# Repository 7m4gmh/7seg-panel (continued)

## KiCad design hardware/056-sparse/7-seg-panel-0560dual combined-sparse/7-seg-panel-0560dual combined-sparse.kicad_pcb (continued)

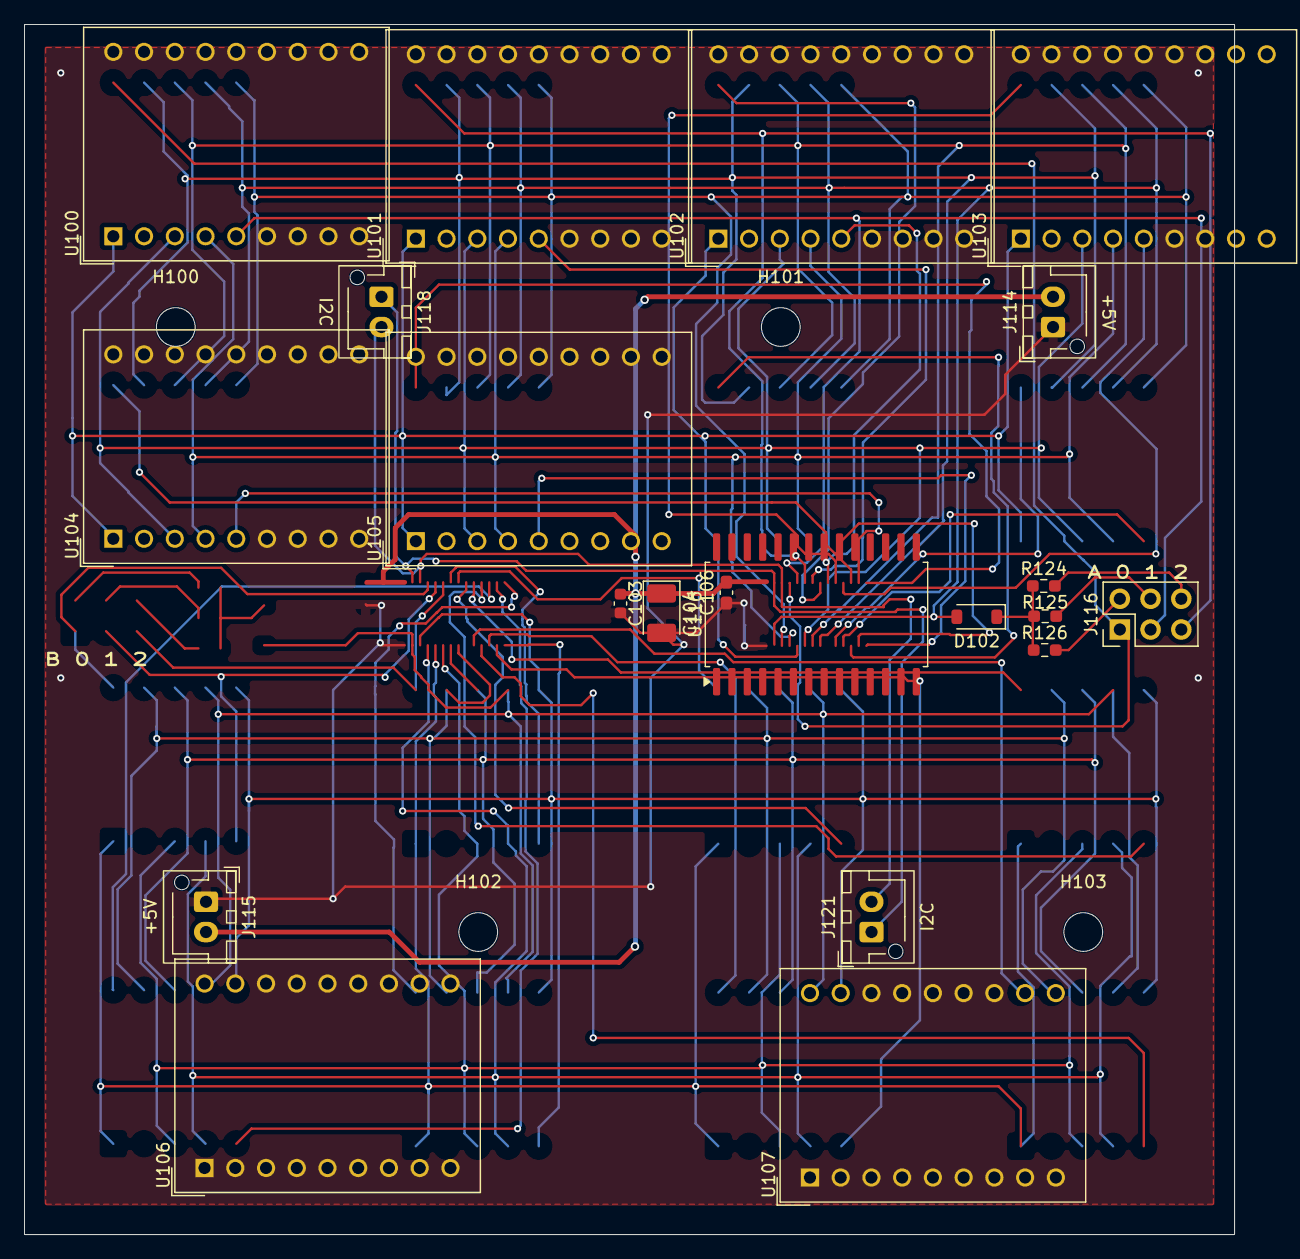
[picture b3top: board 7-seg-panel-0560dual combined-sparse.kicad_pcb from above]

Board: 2 copper layers, 100.0 x 100.0 mm, 25 parts (0 on the bottom side), 31 nets.

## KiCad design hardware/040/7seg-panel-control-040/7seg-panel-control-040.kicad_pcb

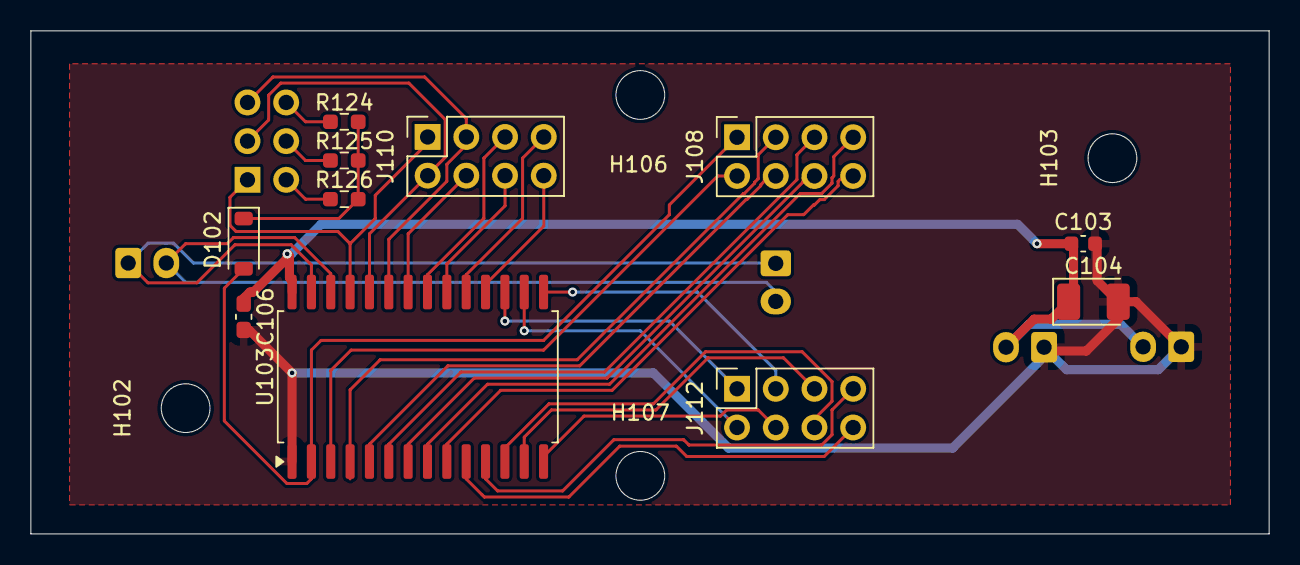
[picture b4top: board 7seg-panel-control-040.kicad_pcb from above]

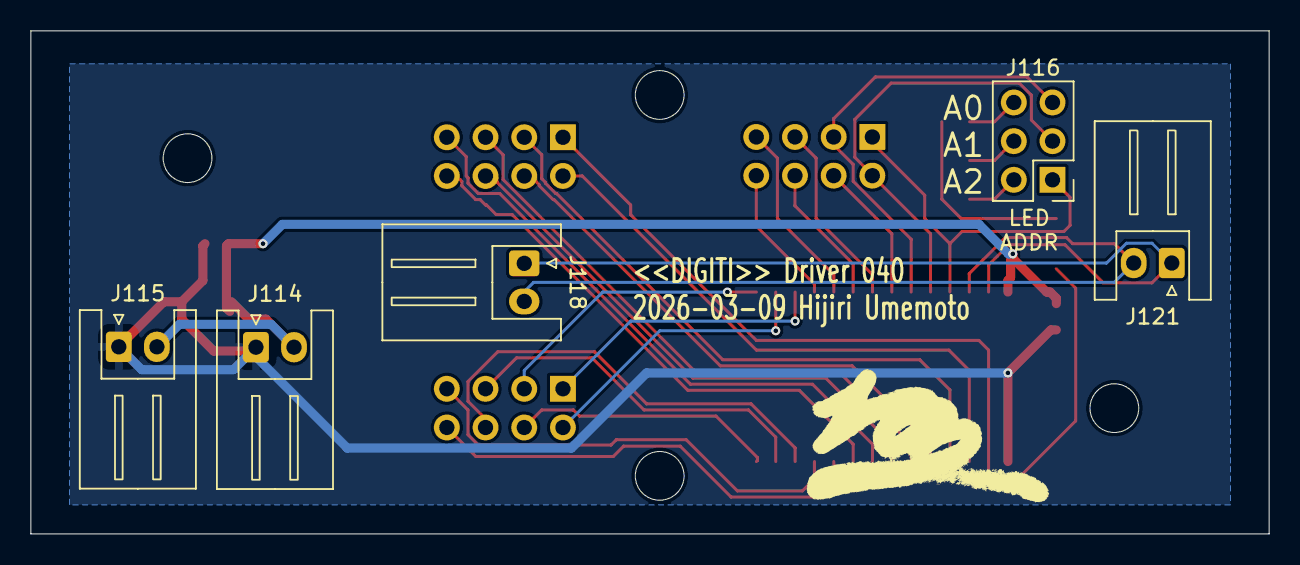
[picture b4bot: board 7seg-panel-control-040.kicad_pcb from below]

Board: 2 copper layers, 81.3 x 33.0 mm, 20 parts (5 on the bottom side), 32 nets.

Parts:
C103: 22uF; C_0603_1608Metric
C104: 22uF; CP_EIA-3528-21_Kemet-B_HandSolder
C106: 0.1uF; C_0603_1608Metric_Pad1.08x0.95mm_HandSolder
D102: 1N4148W; D_SOD-123
H102, H103, H106, H107: MountingHole; MountingHole_3.2mm_M3
J108, J110, J112: Conn_02x04_Odd_Even; PinSocket_2x04_P2.54mm_Vertical
J114, J115: +5V; JST_XH_S2B-XH-A_1x02_P2.50mm_Horizontal
J116: Conn_02x03_Odd_Even; PinHeader_2x03_P2.54mm_Vertical
J118, J121: I2C; JST_XH_S2B-XH-A_1x02_P2.50mm_Horizontal
R124, R125, R126: 39kR; R_0603_1608Metric_Pad0.98x0.95mm_HandSolder
U103: HT16K33-28-SOPA; SOP-28_8.4x18.16mm_P1.27mm

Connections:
COM0: D102.2 (A), J108.1, U103.2 (COM0/AD)
COM1: J108.2, U103.3 (COM1/KS0)
COM2: J108.3, U103.4 (COM2/KS1)
COM3: J108.4, U103.5 (COM3/KS2)
COM4: J108.5, U103.6 (COM4)
COM5: J108.6, U103.7 (COM5)
COM6: J108.7, U103.8 (COM6)
COM7: J108.8, U103.9 (COM7)
GND: C103.2, C104.2, C106.2, J114.1, J115.1, U103.1 (VSS)
unnamed: D102.1 (K), R124.1, R125.1, R126.1
unnamed: J116.2, R126.2
unnamed: J116.4, R125.2
unnamed: J116.6, R124.2
ROW0: J110.1, J116.1, U103.25 (ROW0/A2)
ROW1: J110.2, J116.3, U103.24 (ROW1/A1)
ROW2: J110.3, J116.5, U103.23 (ROW2/A0)
ROW3: J110.4, U103.22 (ROW3/K1)
ROW4: J110.5, U103.21 (ROW4/K2)
ROW5: J110.6, U103.20 (ROW5/K3)
ROW6: J110.7, U103.19 (ROW6/K4)
ROW7: J110.8, U103.18 (ROW7/K5)
ROW8: J112.1, U103.17 (ROW8/K6)
ROW9: J112.2, U103.16 (ROW9/K7)
ROW10: J112.3, U103.15 (ROW10/K8)
ROW11: J112.4, U103.14 (ROW11/K9)
ROW12: J112.5, U103.13 (ROW12/K10)
ROW13: J112.6, U103.12 (ROW13/K12)
ROW14: J112.7, U103.11 (ROW14/K12)
ROW15: J112.8, U103.10 (ROW15/K13/INT)
SCL: J118.2, J121.2, U103.26 (SCL)
SDA: J118.1, J121.1, U103.27 (SDA)
VDD: C103.1, C104.1, C106.1, J114.2, J115.2, U103.28 (VDD)

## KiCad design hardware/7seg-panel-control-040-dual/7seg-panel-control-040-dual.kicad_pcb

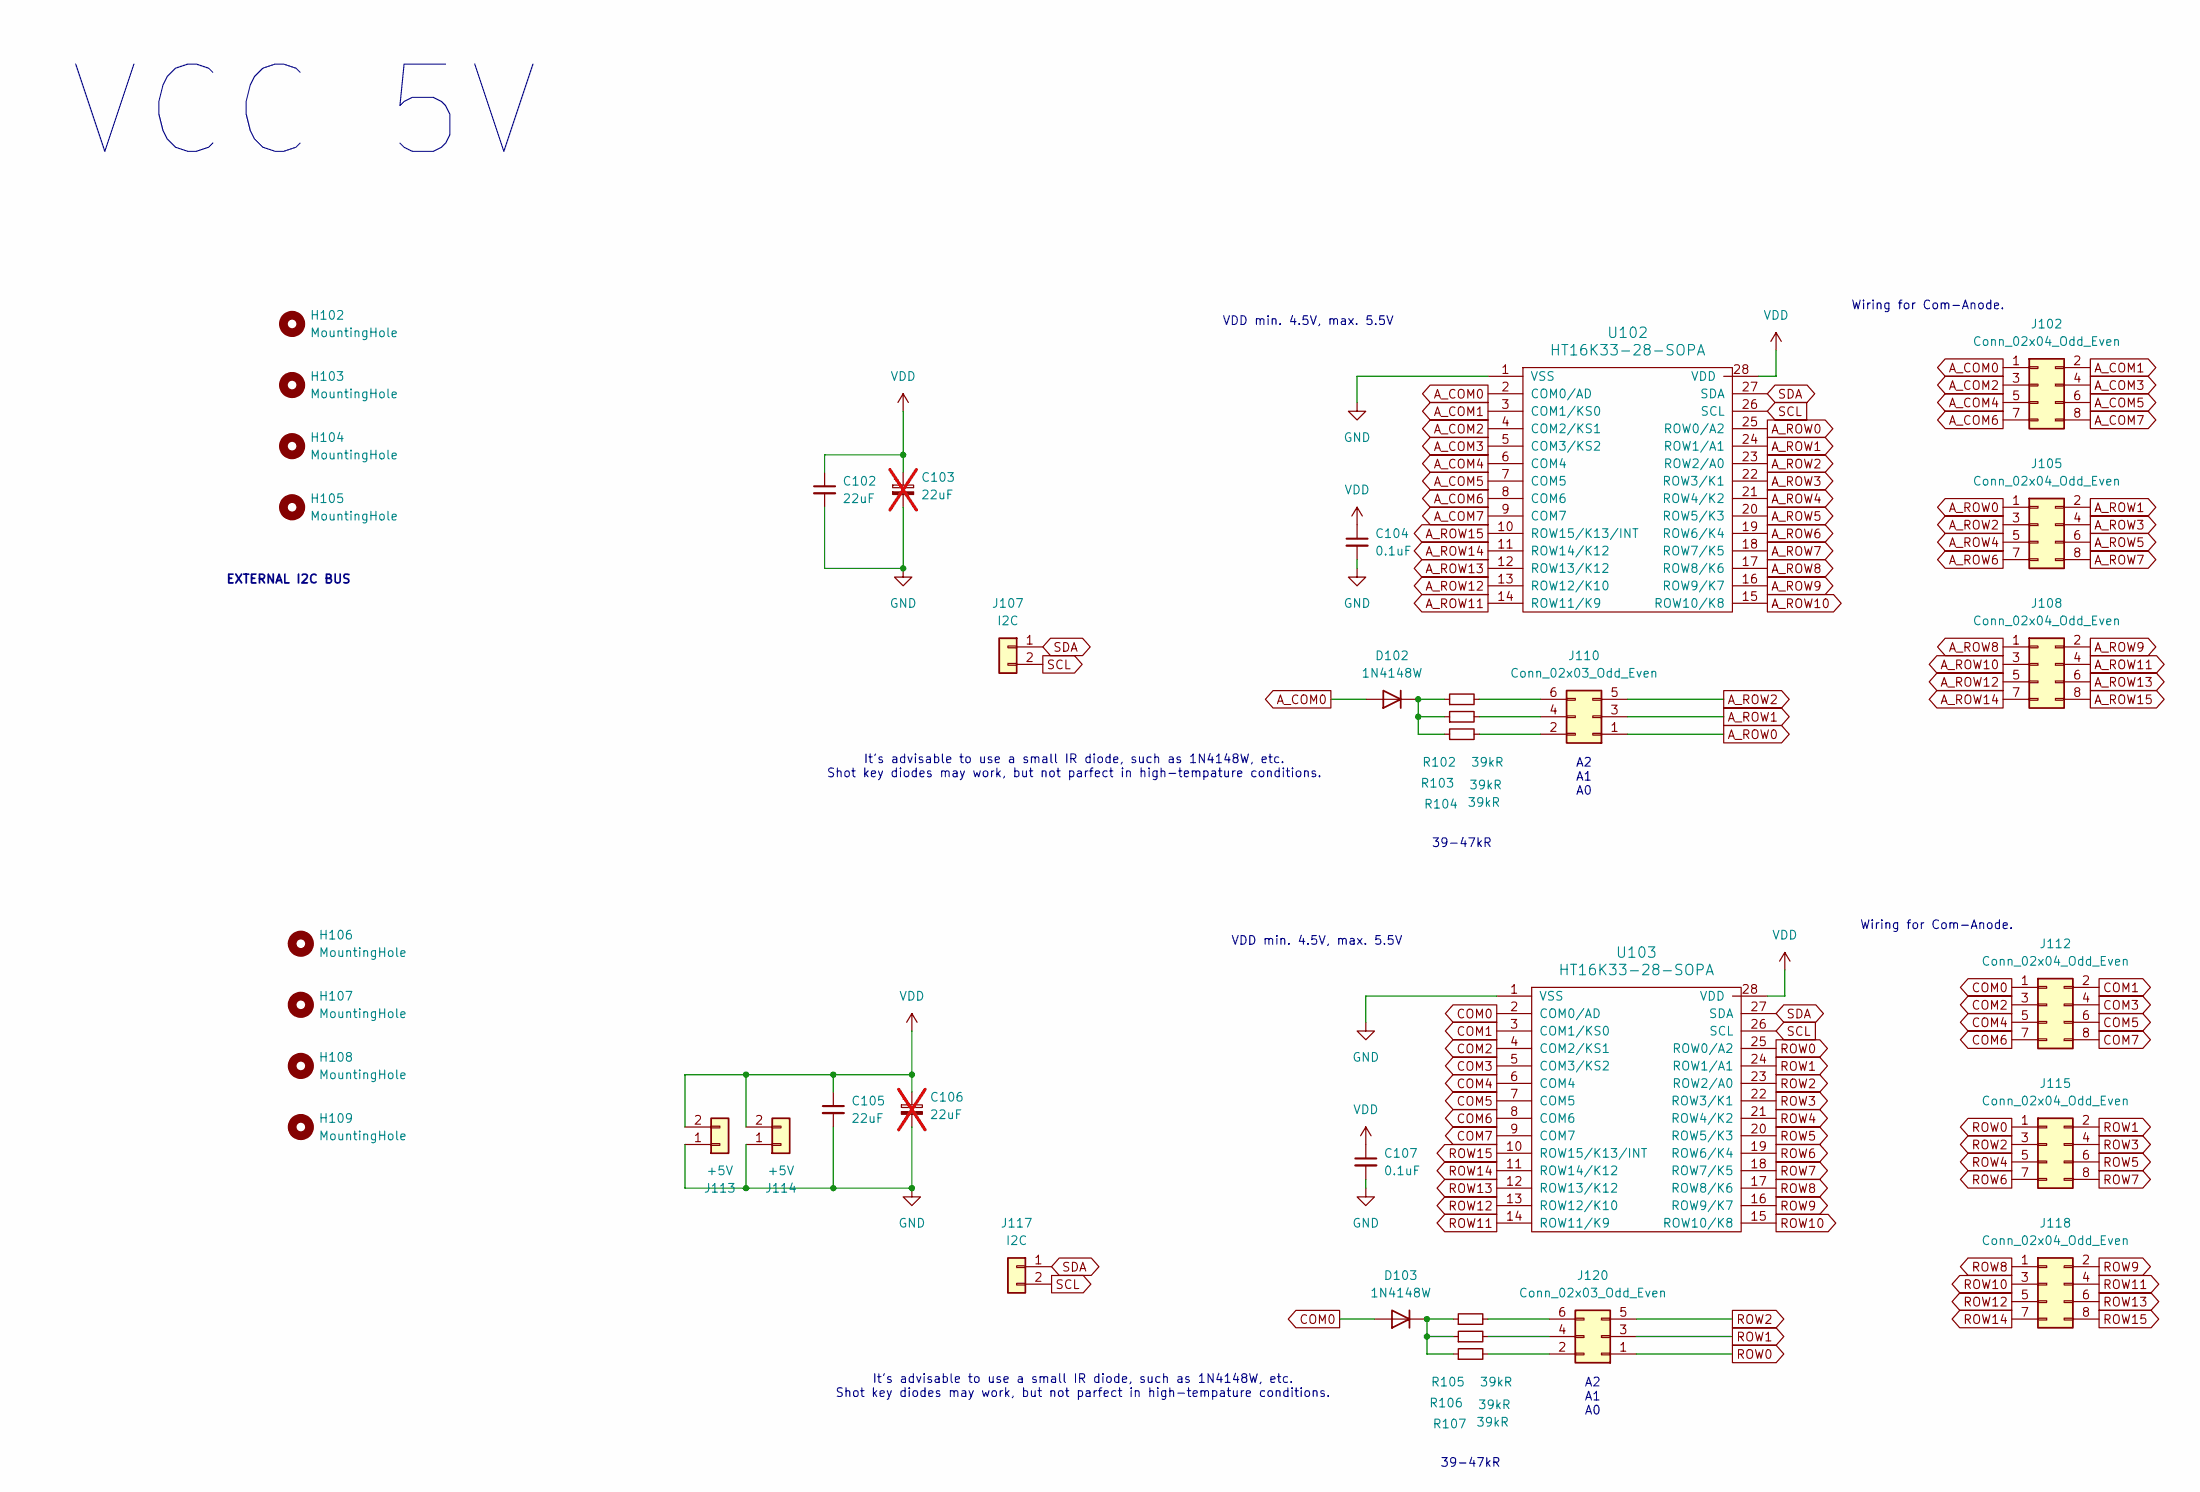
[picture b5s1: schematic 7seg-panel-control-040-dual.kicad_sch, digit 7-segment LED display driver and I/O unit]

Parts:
C102, C105: 22uF; C_0603_1608Metric
C103, C106: 22uF; CP_EIA-3528-21_Kemet-B_HandSolder; not fitted
C104, C107: 0.1uF; C_0603_1608Metric_Pad1.08x0.95mm_HandSolder
D102, D103: 1N4148W; D_SOD-123
H102, H103, H104, H105, H106, H107, H108, H109: MountingHole; MountingHole_3.2mm_M3
J102, J105, J108, J112, J115, J118: Conn_02x04_Odd_Even; PinSocket_2x04_P2.54mm_Vertical
J107, J117: I2C; Generic_XH_S2B-XH-A-1_1x02_P2.50mm_Horizontal
J110, J120: Conn_02x03_Odd_Even; PinHeader_2x03_P2.54mm_Vertical
J113, J114: +5V; Generic_XH_S2B-XH-A-1_1x02_P2.50mm_Horizontal
R102, R103, R104, R105, R106, R107: 39kR; R_0603_1608Metric_Pad0.98x0.95mm_HandSolder
U102, U103: HT16K33-28-SOPA; SOP-28_8.4x18.16mm_P1.27mm

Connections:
A_COM0: D102.2 (A), J102.1, U102.2 (COM0/AD)
A_COM1: J102.2, U102.3 (COM1/KS0)
A_COM2: J102.3, U102.4 (COM2/KS1)
A_COM3: J102.4, U102.5 (COM3/KS2)
A_COM4: J102.5, U102.6 (COM4)
A_COM5: J102.6, U102.7 (COM5)
A_COM6: J102.7, U102.8 (COM6)
A_COM7: J102.8, U102.9 (COM7)
A_ROW0: J105.1, J110.1, U102.25 (ROW0/A2)
A_ROW1: J105.2, J110.3, U102.24 (ROW1/A1)
A_ROW2: J105.3, J110.5, U102.23 (ROW2/A0)
A_ROW3: J105.4, U102.22 (ROW3/K1)
A_ROW4: J105.5, U102.21 (ROW4/K2)
A_ROW5: J105.6, U102.20 (ROW5/K3)
A_ROW6: J105.7, U102.19 (ROW6/K4)
A_ROW7: J105.8, U102.18 (ROW7/K5)
A_ROW8: J108.1, U102.17 (ROW8/K6)
A_ROW9: J108.2, U102.16 (ROW9/K7)
A_ROW10: J108.3, U102.15 (ROW10/K8)
A_ROW11: J108.4, U102.14 (ROW11/K9)
A_ROW12: J108.5, U102.13 (ROW12/K10)
A_ROW13: J108.6, U102.12 (ROW13/K12)
A_ROW14: J108.7, U102.11 (ROW14/K12)
A_ROW15: J108.8, U102.10 (ROW15/K13/INT)
COM0: D103.2 (A), J112.1, U103.2 (COM0/AD)
COM1: J112.2, U103.3 (COM1/KS0)
COM2: J112.3, U103.4 (COM2/KS1)
COM3: J112.4, U103.5 (COM3/KS2)
COM4: J112.5, U103.6 (COM4)
COM5: J112.6, U103.7 (COM5)
COM6: J112.7, U103.8 (COM6)
COM7: J112.8, U103.9 (COM7)
GND: C102.2, C103.2, C104.2, C105.2, C106.2, C107.2, J113.1, J114.1, U102.1 (VSS), U103.1 (VSS)
unnamed: D102.1 (K), R102.1, R103.1, R104.1
unnamed: D103.1 (K), R105.1, R106.1, R107.1
unnamed: J110.2, R104.2
unnamed: J110.4, R103.2
unnamed: J110.6, R102.2
unnamed: J120.2, R107.2
unnamed: J120.4, R106.2
unnamed: J120.6, R105.2
ROW0: J115.1, J120.1, U103.25 (ROW0/A2)
ROW1: J115.2, J120.3, U103.24 (ROW1/A1)
ROW2: J115.3, J120.5, U103.23 (ROW2/A0)
ROW3: J115.4, U103.22 (ROW3/K1)
ROW4: J115.5, U103.21 (ROW4/K2)
ROW5: J115.6, U103.20 (ROW5/K3)
ROW6: J115.7, U103.19 (ROW6/K4)
ROW7: J115.8, U103.18 (ROW7/K5)
ROW8: J118.1, U103.17 (ROW8/K6)
ROW9: J118.2, U103.16 (ROW9/K7)
ROW10: J118.3, U103.15 (ROW10/K8)
ROW11: J118.4, U103.14 (ROW11/K9)
ROW12: J118.5, U103.13 (ROW12/K10)
ROW13: J118.6, U103.12 (ROW13/K12)
ROW14: J118.7, U103.11 (ROW14/K12)
ROW15: J118.8, U103.10 (ROW15/K13/INT)
SCL: J107.2, J117.2, U102.26 (SCL), U103.26 (SCL)
SDA: J107.1, J117.1, U102.27 (SDA), U103.27 (SDA)
VDD: C102.1, C103.1, C104.1, C105.1, C106.1, C107.1, J113.2, J114.2, U102.28 (VDD), U103.28 (VDD)

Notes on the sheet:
VDD min. 4.5V, max. 5.5V
Wiring for Com-Anode.
39-47kR
It's advisable to use a small IR diode, such as 1N4148W, etc. Shot key diodes may work, but not parfect in high-tempature conditions.
A2 A1 A0
VCC 5V
EXTERNAL I2C BUS

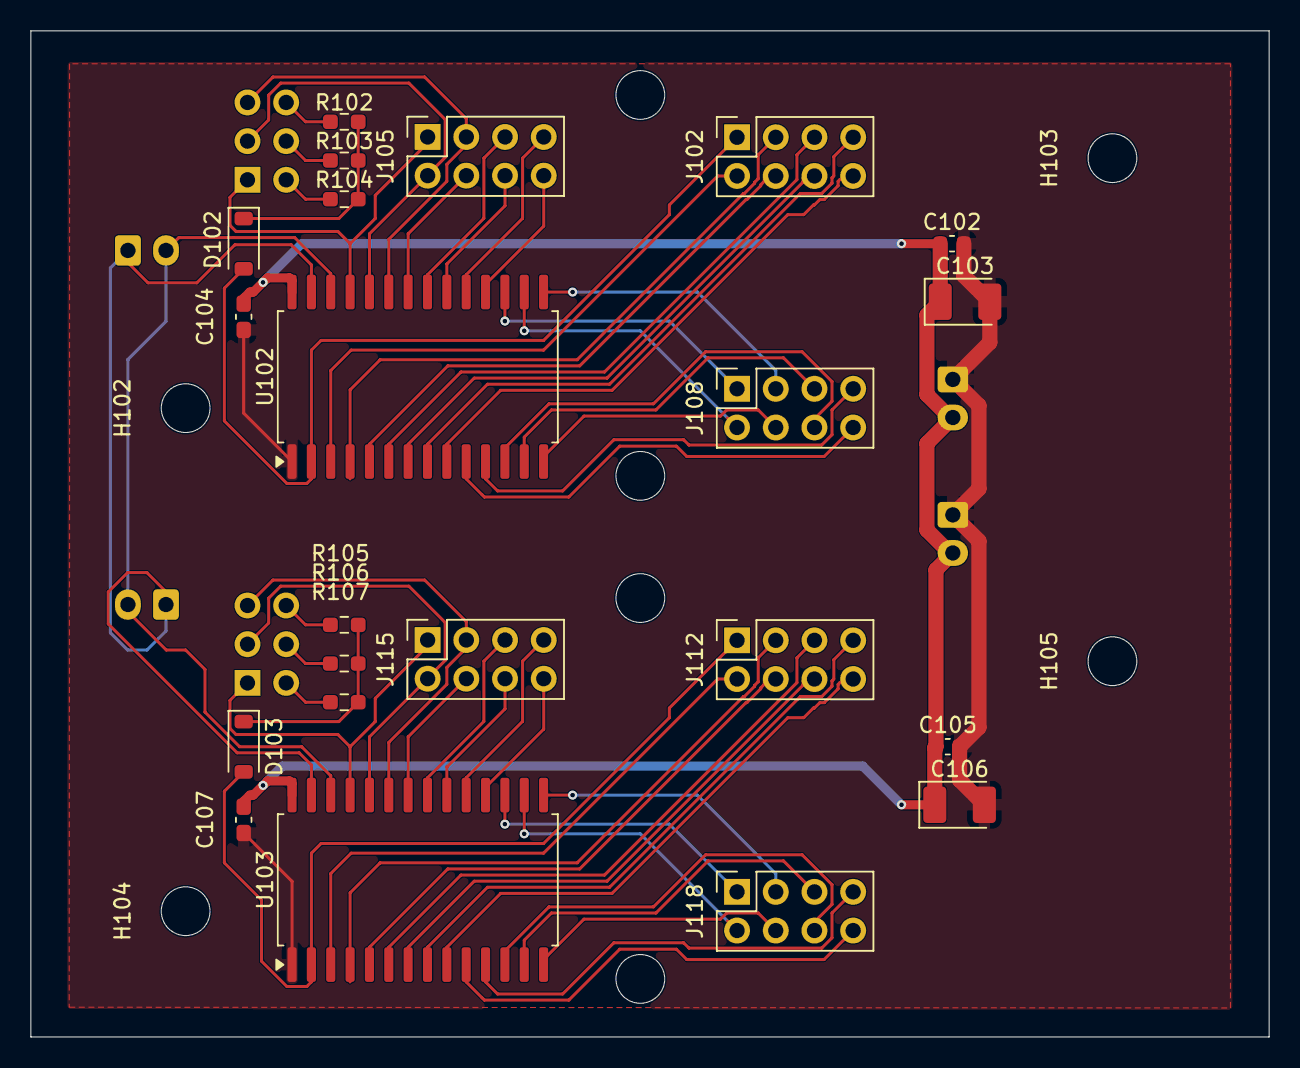
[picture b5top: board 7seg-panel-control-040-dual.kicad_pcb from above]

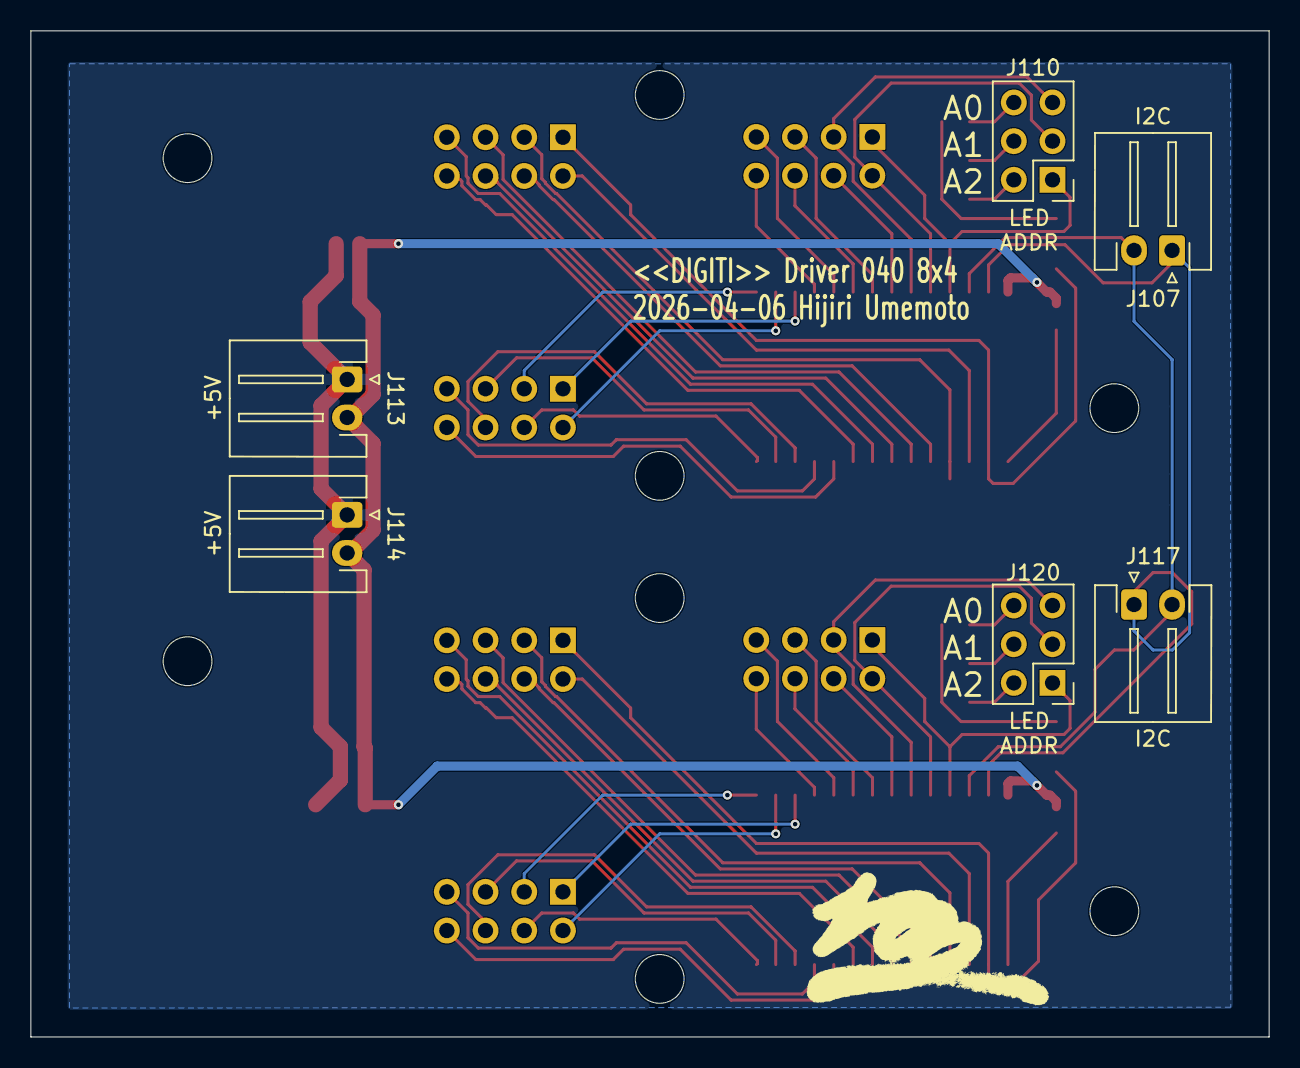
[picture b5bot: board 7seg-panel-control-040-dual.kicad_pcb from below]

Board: 2 copper layers, 81.3 x 66.0 mm, 36 parts (6 on the bottom side), 60 nets.

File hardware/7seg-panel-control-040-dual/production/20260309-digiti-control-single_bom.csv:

Designator,Footprint,Quantity,Value,LCSC Part #
"C102, C105",0603,2,22uF,
"C104, C107",0603,2,0.1uF,
"D102, D103",D_SOD-123,2,1N4148W,
"J102, J105, J108, J112, J115, J118",PinSocket_2x04_P2.54mm_Vertical,6,Conn_02x04_Odd_Even,
"J107, J117",Generic_XH_S2B-XH-A-1_1x02_P2.50mm_Horizontal,2,I2C,
"J110, J120",PinHeader_2x03_P2.54mm_Vertical,2,Conn_02x03_Odd_Even,
"J113, J114",Generic_XH_S2B-XH-A-1_1x02_P2.50mm_Horizontal,2,+5V,
"R102, R103, R104, R105, R106, R107",0603,6,39kR,
"U102, U103",SOP-28_8.4x18.16mm_P1.27mm,2,HT16K33-28-SOPA,

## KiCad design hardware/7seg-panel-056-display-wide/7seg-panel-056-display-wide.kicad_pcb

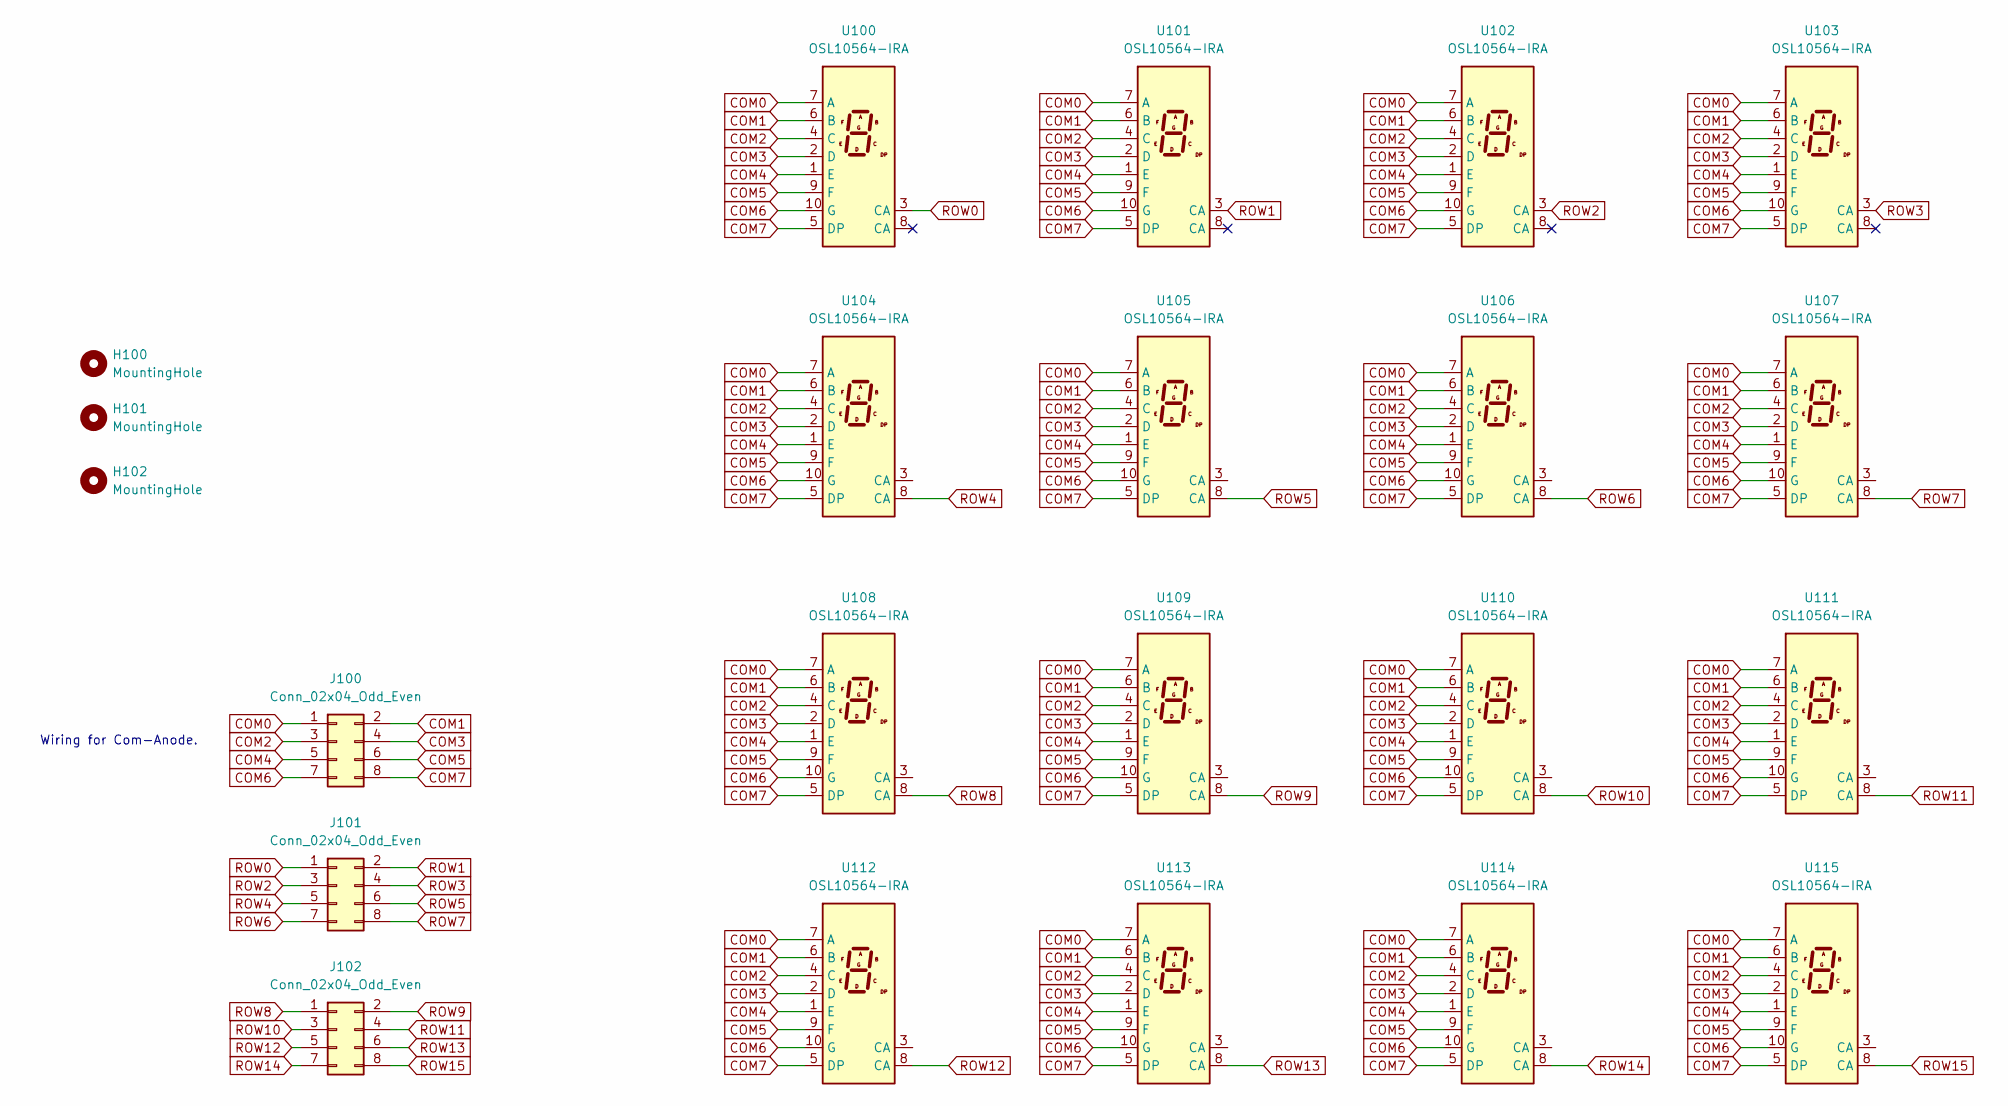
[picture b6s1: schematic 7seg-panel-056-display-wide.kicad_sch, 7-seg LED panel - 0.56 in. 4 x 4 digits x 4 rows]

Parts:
H100, H101, H102: MountingHole; MountingHole_3.2mm_M3
J100, J101, J102: Conn_02x04_Odd_Even; PinHeader_2x04_P2.54mm_Vertical
U100, U101, U102, U103, U104, U105, U106, U107, U108, U109, U110, U111, U112, U113, U114, U115: OSL10564-IRA; 7SegmentLED_OSL10564

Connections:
COM0: J100.1, U100.7 (A), U101.7 (A), U102.7 (A), U103.7 (A), U104.7 (A), U105.7 (A), U106.7 (A), U107.7 (A), U108.7 (A), U109.7 (A), U110.7 (A), U111.7 (A), U112.7 (A), U113.7 (A), U114.7 (A), U115.7 (A)
COM1: J100.2, U100.6 (B), U101.6 (B), U102.6 (B), U103.6 (B), U104.6 (B), U105.6 (B), U106.6 (B), U107.6 (B), U108.6 (B), U109.6 (B), U110.6 (B), U111.6 (B), U112.6 (B), U113.6 (B), U114.6 (B), U115.6 (B)
COM2: J100.3, U100.4 (C), U101.4 (C), U102.4 (C), U103.4 (C), U104.4 (C), U105.4 (C), U106.4 (C), U107.4 (C), U108.4 (C), U109.4 (C), U110.4 (C), U111.4 (C), U112.4 (C), U113.4 (C), U114.4 (C), U115.4 (C)
COM3: J100.4, U100.2 (D), U101.2 (D), U102.2 (D), U103.2 (D), U104.2 (D), U105.2 (D), U106.2 (D), U107.2 (D), U108.2 (D), U109.2 (D), U110.2 (D), U111.2 (D), U112.2 (D), U113.2 (D), U114.2 (D), U115.2 (D)
COM4: J100.5, U100.1 (E), U101.1 (E), U102.1 (E), U103.1 (E), U104.1 (E), U105.1 (E), U106.1 (E), U107.1 (E), U108.1 (E), U109.1 (E), U110.1 (E), U111.1 (E), U112.1 (E), U113.1 (E), U114.1 (E), U115.1 (E)
COM5: J100.6, U100.9 (F), U101.9 (F), U102.9 (F), U103.9 (F), U104.9 (F), U105.9 (F), U106.9 (F), U107.9 (F), U108.9 (F), U109.9 (F), U110.9 (F), U111.9 (F), U112.9 (F), U113.9 (F), U114.9 (F), U115.9 (F)
COM6: J100.7, U100.10 (G), U101.10 (G), U102.10 (G), U103.10 (G), U104.10 (G), U105.10 (G), U106.10 (G), U107.10 (G), U108.10 (G), U109.10 (G), U110.10 (G), U111.10 (G), U112.10 (G), U113.10 (G), U114.10 (G), U115.10 (G)
COM7: J100.8, U100.5 (DP), U101.5 (DP), U102.5 (DP), U103.5 (DP), U104.5 (DP), U105.5 (DP), U106.5 (DP), U107.5 (DP), U108.5 (DP), U109.5 (DP), U110.5 (DP), U111.5 (DP), U112.5 (DP), U113.5 (DP), U114.5 (DP), U115.5 (DP)
ROW0: J101.1, U100.3 (CA)
ROW1: J101.2, U101.3 (CA)
ROW2: J101.3, U102.3 (CA)
ROW3: J101.4, U103.3 (CA)
ROW4: J101.5, U104.8 (CA)
ROW5: J101.6, U105.8 (CA)
ROW6: J101.7, U106.8 (CA)
ROW7: J101.8, U107.8 (CA)
ROW8: J102.1, U108.8 (CA)
ROW9: J102.2, U109.8 (CA)
ROW10: J102.3, U110.8 (CA)
ROW11: J102.4, U111.8 (CA)
ROW12: J102.5, U112.8 (CA)
ROW13: J102.6, U113.8 (CA)
ROW14: J102.7, U114.8 (CA)
ROW15: J102.8, U115.8 (CA)

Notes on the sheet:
Wiring for Com-Anode.

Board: 2 copper layers, 22 parts (3 on the bottom side), 24 nets, no tracks yet.

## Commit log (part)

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2025-08-22 単一ファイルからモジュール化した。
2025-08-22 モジュール化。
2025-08-23 server binaries
2025-08-23 file integration
2025-08-24 youtube streaming
2025-08-24 camera control
2025-08-25 video control, revised.
2025-08-26 focus fix
2025-08-27 tetris
2025-08-27 panel allignment config
2025-08-27 packaging and multilingual README
2025-08-30 panel expansion scheme
2025-08-30 multiple panel configuration
2025-08-31 tetris vertical
2025-08-31 read configuration from json
2025-08-31 read playlist from youtube then play videos
2025-09-01 update panel config
2025-09-02 i2c error recovory
2025-09-02 build process refactoring
2025-09-03 README
2025-09-03 revised dead link
2025-09-03 tetris gravity
2025-09-05 clock
2025-09-06 rtp test
2025-09-06 implement RTP
2025-09-06 x264enc fix
2025-09-07 rtp and net implement - not perfect
2025-09-07 test gst
2025-09-07 feat: add macOS camera RTP sender script (H.264+Opus, 320x240@15fps, FEC, VTenc fallback)
2025-09-07 cam test
2025-09-07 purge 7seg-http-streamer
2025-09-07 ignore ./vscode/
2025-09-07 ignore obj/
2025-09-07 net_player.cpp rewrite
2025-09-08 test tools
2025-09-08 obs relay
2025-09-08 test tool passthrough
2025-09-08 flv test
2025-09-08 7seg-net-player run as a network service
2025-09-08 hardware
2025-09-08 hardware README
2025-09-08 remove unused files
2025-09-08 revise README
2025-09-08 PCB version up
2025-09-08 dependabot
2025-09-08 Bump actions/checkout from 4 to 5
    Bumps [actions/checkout](https://github.com/actions/checkout) from 4 to 5.
    - [Release notes](https://github.com/actions/checkout/releases)
    - [Changelog](https://github.com/actions/checkout/blob/main/CHANGELOG.md)
    - [Commits](https://github.com/actions/checkout/compare/v4...v5)
    ---
    updated-dependencies:
2025-09-09 Update CodeQL workflow to handle Makefile location
2025-09-09 Simplify Makefile build process in CodeQL workflow
2025-09-15 emulator
2025-09-15 GPU enable on emulator
2025-09-16 Ruspberry Pi and multiple i2c bus support
2025-09-17 feat: Refactor config.json to Bus-based structure supporting multiple TCA9548A
    - Update DisplayConfig struct to use buses with TCA9548A lists
    - Modify config_loader.hpp to parse buses configuration
    - Fix LED offset calculations in led.cpp for proper module positioning
    - Correct ROI calculation in video.cpp to prevent out-of-bounds access for D segment
    - Update test_i2c.cpp to display TCA addresses from buses
    - Add README.config.md for configuration documentation
2025-09-17 panel config revised for production model
2025-09-17 enable emulator mode on 7seg-http-player
2025-09-17 Optimize video processing and emulator rendering performance
    - Video processing optimizations:
    * Add VideoProcessingCache struct to cache ROI calculations and sampling coordinates
    * Pre-compute sampling coordinate tables to eliminate per-frame calculations
    * Optimize frame_to_grid function to use cached coordinates
    * Reduce computational overhead by ~90% for video-to-LED conversion
    - Emulator rendering optimizations:
2025-09-18 Implement differential rendering for emulator performance optimization
2025-09-18 Add RPi5 test preparation and differential rendering optimization
    - Implement differential rendering for improved performance (60.86 FPS)
    - Add RPi5 build script with automated testing and logging
    - Create RPi5 test documentation (RPI5_TEST_README.md)
    - Update README with platform support and quick start guide
    - Add .gitignore to exclude large files (*.tar.gz)
    - Ready for RPi5 build testing (build failure investigation needed)
2025-09-18 Fix RPi5 build script for Debian 12 compatibility
    - Fix GStreamer plugins-good package name issue for Raspberry Pi OS
    - Add fallback logic for different package naming conventions
    - Update .gitignore to exclude build binaries (bin/ directory)
    - Improve dependency installation robustness for RPi5/Debian 12
2025-09-18 Fix binary compatibility issues for RPi5 testing
    - Fix Exec format error by ensuring RPi5 builds its own binaries
    - Add architecture verification for built binaries
    - Improve error handling when binaries are missing
    - Add fallback build process for benchmark and file player tests
    - Enhance logging for build and test failures
2025-09-18 Fix RPi5 compilation errors
    - Add missing #include <string> to emulator_display.h
    - Add explicit CXXFLAGS rule for emulator_benchmark.o compilation
    - Fix signed/unsigned comparison warning in emulator_display.cpp
    - Remove unused tilt_dx variable in emulator_display.cpp and playback.cpp
    - Add CXXFLAGS debug output to Makefile for troubleshooting
    - Ensure proper include paths for RPi5 cross-compilation
2025-09-18 Add Qt headless environment support for RPi5
    - Set QT_QPA_PLATFORM=offscreen for benchmark and emulator tests
    - Configure DISPLAY=:0 as fallback for headless operation
    - Handle Qt display issues in RPi5 headless environment
    - Maintain build success even if Qt GUI tests fail in headless mode
2025-09-18 Complete RPi5 compatibility and performance optimization
    - Add differential rendering for improved performance (60.86 FPS)
    - Fix compilation errors for RPi5/Debian 12 compatibility
    - Add Qt headless environment support for RPi5 testing
    - Update build script with comprehensive testing and logging
    - Add RPi5 test documentation and platform support
    - Fix header includes and compilation warnings
2025-09-21 config only
2025-09-21 Implement 48x8 LED panel support with rows-based layout
    - Add 48x8 configuration with TCA9548A channel multiplexing
    - Update Makefile for platform-specific builds (ROCK5B/RPi5)
    - Fix tetris.py to support new config structure and rows-based display
    - Update README.config.md with 48x8 example and rows documentation
    - Debug and fix LED display issues for proper 48x8 rendering
2025-09-21 Add comprehensive LED screensaver with multiple animation modes and command-line options
    - Implement IP address display with centering
    - Add breakout game with paddle AI and destructible blocks
    - Add invaders game with cannon and enemy AI
    - Add miyajima modes with count-up and scrolling animations
    - Add clock display mode
    - Add command-line options for mode selection and configuration
2025-09-23 i2c bus selection
2025-10-05 video: FIT/CROP/STRETCH fixes; add --debug flag; document behavior in README
2025-10-05 file-player: add --loop/-l option to repeat video playback (file_player only)
2025-10-05 file-player: add debug prints to diagnose --loop behavior
2025-10-05 file-player: remove unnecessary watchdog thread to avoid join blocking after playback
2025-10-05 file-player: ensure loop exits on g_should_exit (Ctrl-C)
2025-10-05 Integrate FIT/CROP/STRETCH fixes, add --debug and file-player --loop; update README
2025-10-05 ci(codeql): disable autobuild and install build deps (clang, opencv, sdl2, gstreamer)
2025-10-05 ci(codeql): run explicit 'make all' with clang toolchain so CodeQL can capture compile commands
2025-10-05 ci(codeql): fetch cpp-httplib header and force clang++ when building for analysis
2025-10-05 chore: ignore local test media and KiCad fp caches
2025-10-05 chore: add hardware files and config changes
2025-10-05 ignore *.deb
2025-10-13 Bump github/codeql-action from 3 to 4
    Bumps [github/codeql-action](https://github.com/github/codeql-action) from 3 to 4.
    - [Release notes](https://github.com/github/codeql-action/releases)
    - [Changelog](https://github.com/github/codeql-action/blob/main/CHANGELOG.md)
    - [Commits](https://github.com/github/codeql-action/compare/v3...v4)
    ---
    updated-dependencies:
2025-11-24 Bump actions/checkout from 5 to 6
    Bumps [actions/checkout](https://github.com/actions/checkout) from 5 to 6.
    - [Release notes](https://github.com/actions/checkout/releases)
    - [Changelog](https://github.com/actions/checkout/blob/main/CHANGELOG.md)
    - [Commits](https://github.com/actions/checkout/compare/v5...v6)
    ---
    updated-dependencies:
2026-03-02 hardware panel 040 size added
2026-03-02 消灯処理
2026-03-02 パネル設定の拡張
2026-03-02 add 4x4-direct to config.json
2026-03-02 revise config
2026-03-04 パネル定義追加
2026-03-04 test script
2026-03-04 i2ctest
2026-03-04 python script
2026-03-04 live test script
2026-03-04 4桁と8桁ごとの処理を行うよう修正
2026-03-04 reverseオプション追加
2026-03-04 revised mapping rules
2026-03-04 逆順の設定を追加
2026-03-04 Add config-driven module mapping, mapping tests and docs
2026-03-19 ファイル再生時の音声と動画の同期確認
2026-03-19 遅延対策 パイプラインの時間まち
2026-03-24 config
2026-04-05 Add led_sequencer with i2c mapping and README
2026-04-05 Ignore .history directories
2026-04-05 hardware: KiCad ファイルの更新と不要ファイルの削除
2026-04-05 Fix: move main() guard to EOF so helper functions are defined before use
2026-04-05 Make i2c writes digit-specific (use apply_grid_to_modules); include DP; ALL ON uses 0xFF
2026-04-05 Fix: parse module addresses to integers in apply_grid_to_modules before I2C writes
2026-04-10 added pcb designs
2026-04-10 debug
2026-04-10 debug config
2026-04-10 config.json
2026-04-10 test
2026-04-10 test confi
2026-04-15 config only.
2026-04-15 file-player: async I2C writer to avoid blocking video
2026-04-16 Add led_batch_test.py: batch test lighting segments A..DP on all digits
2026-04-20 Add 48x16-ch-grid panel configuration
2026-04-20 Add 48x8-ch-grid panel configuration
2026-04-21 Update platform note for Raspberry Pi support
